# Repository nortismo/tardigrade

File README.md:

# Tardigrade

Tardigrade is an open hardware low-power board featuring NXP's LPC55S16 MCU, Semtech's SX1262 LoRa transceiver, u-blox's MAX-8Q GNSS module and Microchip's ATECC608A secure-element. It can be used as it is already or modified to your own needs. 

## Hardware

Schema and layout was created using [KiCad](https://kicad.org/).

## Software

There's a port of the official LoRaWAN stack implementation "LoRaMac-node" from Semtech for the Tardigrade board. The software is managed in a separate [GitHub repository](https://github.com/nortismo/LoRaMac-node).

## License

This hardware is licensed under the [TAPR Open Hardware License](https://tapr.org/the-tapr-open-hardware-license/). Please see the [LICENSE.txt](LICENSE.txt) file.

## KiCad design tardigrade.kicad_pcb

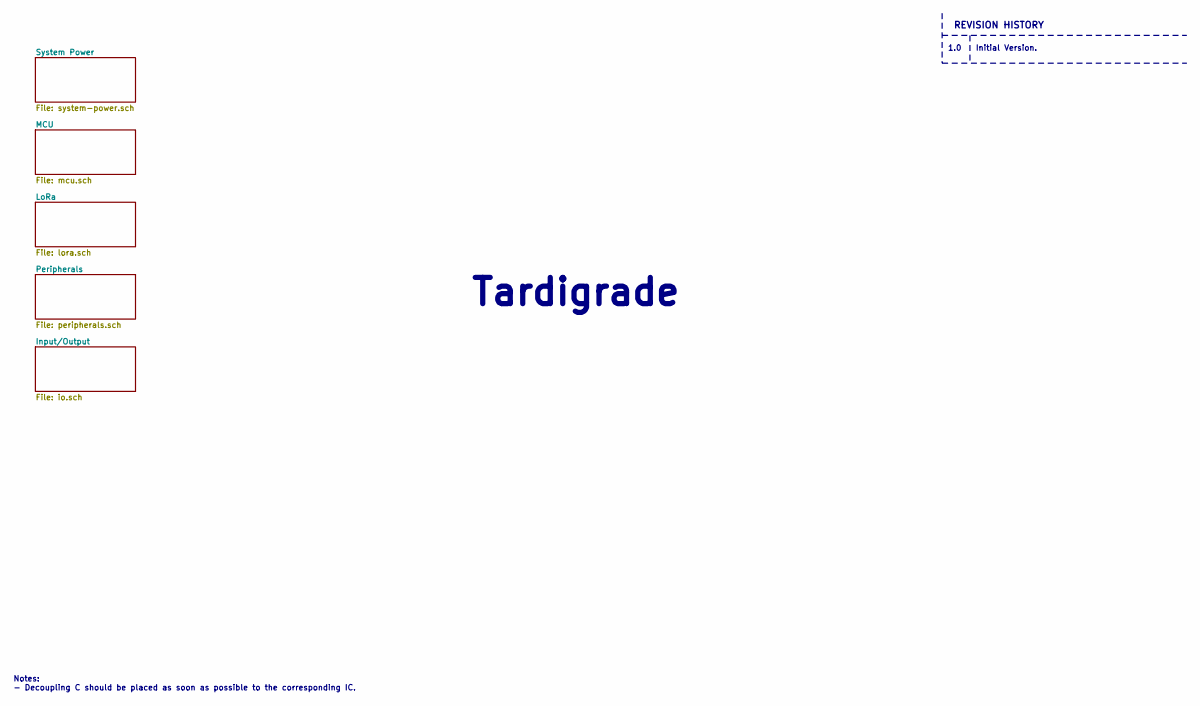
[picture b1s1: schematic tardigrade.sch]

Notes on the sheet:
REVISION HISTORY
1.0
Initial Version.
Tardigrade
Notes: - Decoupling C should be placed as soon as possible to the corresponding IC.

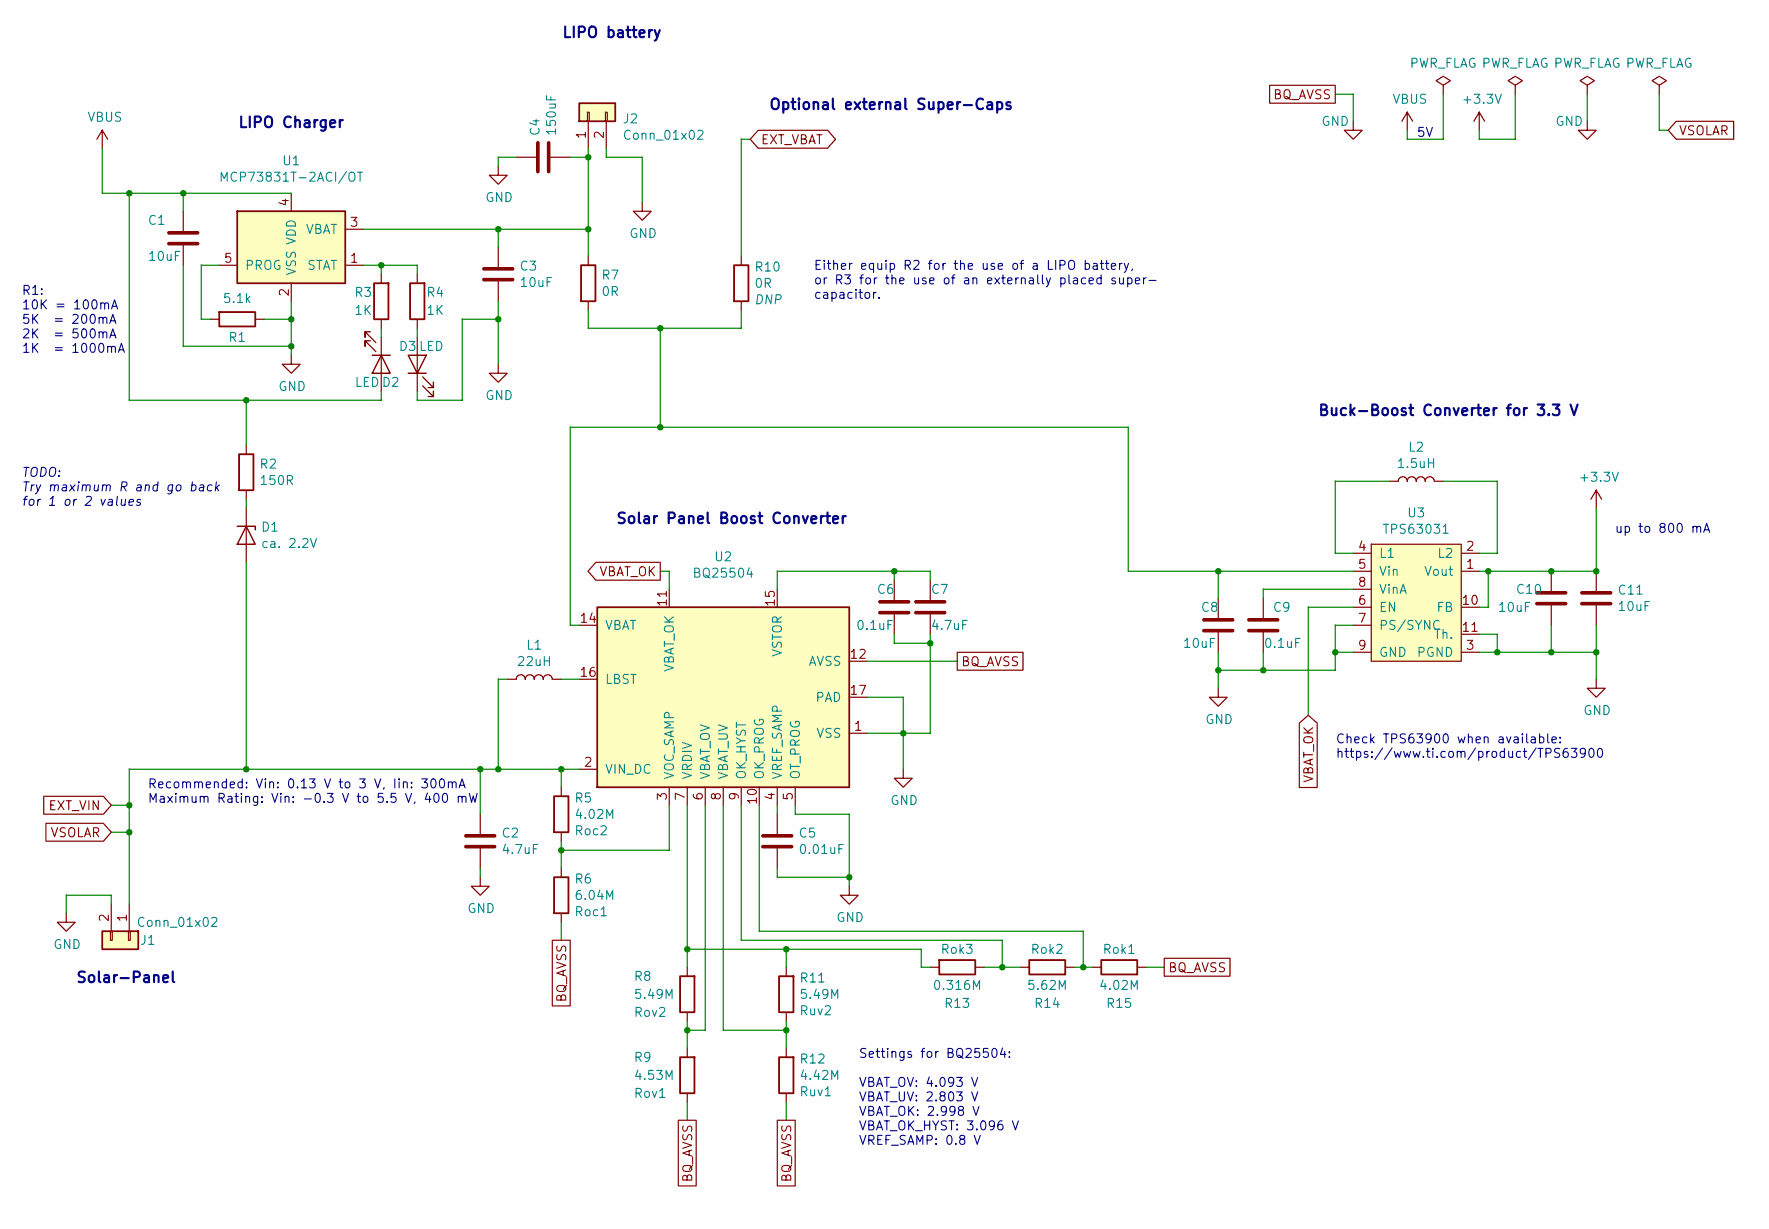
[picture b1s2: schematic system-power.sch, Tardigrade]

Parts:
C1, C3, C8, C10, C11: 10uF; C_0402_1005Metric
C2, C7: 4.7uF; C_0402_1005Metric
C4: 150uF; C_1206_3216Metric
C5: 0.01uF; C_0402_1005Metric
C6, C9: 0.1uF; C_0402_1005Metric
D1: ca. 2.2V; D_SOD-323
D2, D3: LED; LED_0603_1608Metric
J1, J2: Conn_01x02; JST_PH_S2B-PH-K_1x02_P2.00mm_Horizontal
L1: 22uH; L_0805_2012Metric
L2: 1.5uH; L_0402_1005Metric
R1: 5.1k; R_0402_1005Metric
R2: 150R; R_0402_1005Metric
R3, R4: 1K; R_0402_1005Metric
R5, R15: 4.02M; R_0402_1005Metric
R6: 6.04M; R_0402_1005Metric
R7, R10: 0R; R_0402_1005Metric
R8, R11: 5.49M; R_0402_1005Metric
R9: 4.53M; R_0402_1005Metric
R12: 4.42M; R_0402_1005Metric
R13: 0.316M; R_0402_1005Metric
R14: 5.62M; R_0402_1005Metric
U1: MCP73831T-2ACI/OT; SOT-23-5
U2: BQ25504; QFN50P300X300X100-17N-D
U3: TPS63031; TPS63031DSKR

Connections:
BQ_AVSS: C1.2, C2.2, C3.2, C4.1, C5.2, C6.2, C7.2, C8.2, C9.2, C10.2, C11.2, D3.1 (K), J1.2, J2.2, R1.1, R6.2, R9.1, R12.1, R15.2, U1.2 (VSS), U2.1 (VSS), U2.5 (OT_PROG), U2.12 (AVSS), U2.13 (VSS), U2.17 (PAD), U3.3 (PGND), U3.7 (PS/SYNC), U3.9 (GND), U3.11 (Th.); also elsewhere on the board
EXT_VBAT: R10.1; also elsewhere on the board
EXT_VIN: C2.1, D1.2 (A), J1.1, L1.1, R5.1, U2.2 (VIN_DC); also elsewhere on the board
unnamed: C3.1, C4.2, J2.1, R7.1, U1.3 (VBAT)
unnamed: C5.1, U2.4 (VREF_SAMP)
unnamed: C6.1, C7.1, U2.15 (VSTOR)
unnamed: C8.1, R7.2, R10.2, U2.14 (VBAT), U3.5 (Vin)
unnamed: C9.1, U3.8 (VinA)
unnamed: D1.1 (K), R2.2
unnamed: D2.1 (K), R3.1
unnamed: D3.2 (A), R4.1
unnamed: L1.2, U2.16 (LBST)
unnamed: L2.1, U3.4 (L1)
unnamed: L2.2, U3.2 (L2)
unnamed: R1.2, U1.5 (PROG)
unnamed: R3.2, R4.2, U1.1 (STAT)
unnamed: R5.2, R6.1, U2.3 (VOC_SAMP)
unnamed: R8.1, R9.2, U2.6 (VBAT_OV)
unnamed: R11.1, R12.2, U2.8 (VBAT_UV)
unnamed: R8.2, R11.2, R13.2, U2.7 (VRDIV)
unnamed: R13.1, R14.1, U2.9 (OK_HYST)
unnamed: R14.2, R15.1, U2.10 (OK_PROG)
VBAT_OK: U2.11 (VBAT_OK), U3.6 (EN); also elsewhere on the board
VBUS: C1.1, D2.2 (A), R2.1, U1.4 (VDD); also elsewhere on the board

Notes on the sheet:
R1: 10K = 100mA 5K = 200mA 2K = 500mA 1K = 1000mA
LIPO battery
Optional external Super-Caps
up to 800 mA
Recommended: Vin: 0.13 V to 3 V, Iin: 300mA Maximum Rating: Vin: -0.3 V to 5.5 V, 400 mW
Check TPS63900 when available: https://www.ti.com/product/TPS63900
LIPO Charger
Solar-Panel
Solar Panel Boost Converter
Buck-Boost Converter for 3.3 V
Settings for BQ25504: VBAT_OV: 4.093 V VBAT_UV: 2.803 V VBAT_OK: 2.998 V VBAT_OK_HYST: 3.096 V VREF_SAMP: 0.8 V
Either equip R2 for the use of a LIPO battery, or R3 for the use of an externally placed super- capacitor.
TODO: Try maximum R and go back for 1 or 2 values

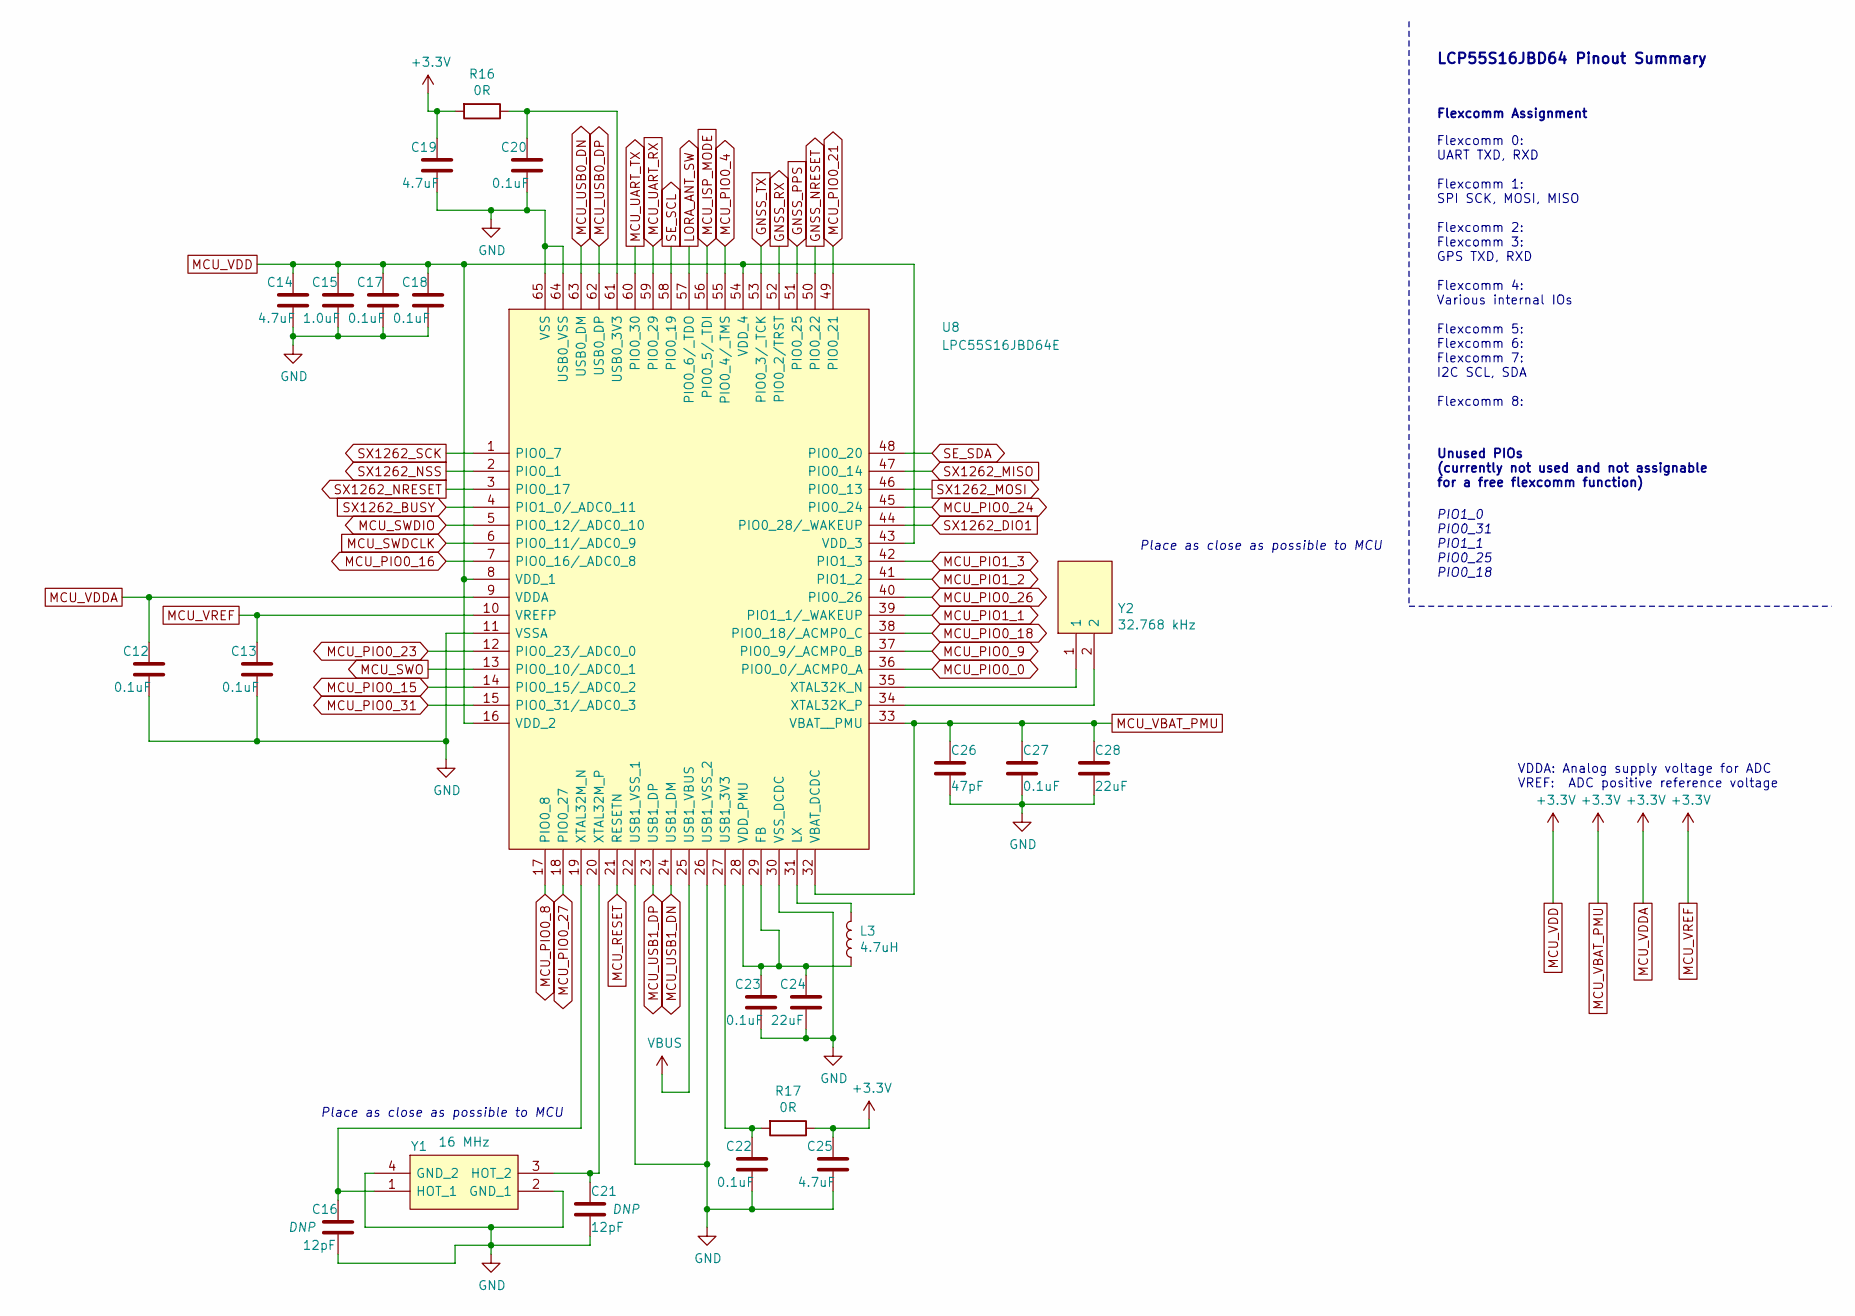
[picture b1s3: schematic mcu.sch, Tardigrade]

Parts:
C12, C13, C17, C18, C20, C22, C23, C27: 0.1uF; C_0402_1005Metric
C14, C19, C25: 4.7uF; C_0402_1005Metric
C15: 1.0uF; C_0402_1005Metric
C16, C21: 12pF; C_0402_1005Metric
C24, C28: 22uF; C_0603_1608Metric
C26: 47pF; C_0402_1005Metric
L3: 4.7uH; L_0805_2012Metric
R16, R17: 0R; R_0402_1005Metric
U8: LPC55S16JBD64E; QFP50P1200X1200X120-65N; Manufacturer_Part_Number LPC55S16JBD64E; Mouser Part Number 771-LPC55S16JBD64E
Y1: 16 MHz; CX3225SA16000
Y2: 32.768 kHz; FC-135_1; Manufacturer_Part_Number FC-135 32.7680KA-AG3; Mouser Part Number 732-FC135-32.76KAAG3

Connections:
BQ_AVSS: C12.2, C13.2, C14.2, C15.2, C16.2, C17.2, C18.2, C19.2, C20.2, C21.2, C22.2, C23.2, C24.2, C25.2, C26.2, C27.2, C28.2, U8.11 (VSSA), U8.22 (USB1_VSS_1), U8.26 (USB1_VSS_2), U8.30 (VSS_DCDC), U8.64 (USB0_VSS), U8.65 (VSS), Y1.2 (GND_1), Y1.4 (GND_2); also elsewhere on the board
GNSS_NRESET: U8.50 (PIO0_22); also elsewhere on the board
GNSS_PPS: U8.51 (PIO0_25); also elsewhere on the board
GNSS_RX: U8.52 (PIO0_2/TRST); also elsewhere on the board
GNSS_TX: U8.53 (PIO0_3/_TCK); also elsewhere on the board
LORA_ANT_SW: U8.57 (PIO0_6/_TDO); also elsewhere on the board
MCU_ISP_MODE: U8.56 (PIO0_5/_TDI); also elsewhere on the board
MCU_PIO0_0: U8.36 (PIO0_0/_ACMP0_A); also elsewhere on the board
MCU_PIO0_4: U8.55 (PIO0_4/_TMS); also elsewhere on the board
MCU_PIO0_8: U8.17 (PIO0_8); also elsewhere on the board
MCU_PIO0_9: U8.37 (PIO0_9/_ACMP0_B); also elsewhere on the board
MCU_PIO0_15: U8.14 (PIO0_15/_ADC0_2); also elsewhere on the board
MCU_PIO0_16: U8.7 (PIO0_16/_ADC0_8); also elsewhere on the board
MCU_PIO0_18: U8.38 (PIO0_18/_ACMP0_C); also elsewhere on the board
MCU_PIO0_21: U8.49 (PIO0_21); also elsewhere on the board
MCU_PIO0_23: U8.12 (PIO0_23/_ADC0_0); also elsewhere on the board
MCU_PIO0_24: U8.45 (PIO0_24); also elsewhere on the board
MCU_PIO0_26: U8.40 (PIO0_26); also elsewhere on the board
MCU_PIO0_27: U8.18 (PIO0_27); also elsewhere on the board
MCU_PIO0_31: U8.15 (PIO0_31/_ADC0_3); also elsewhere on the board
MCU_PIO1_1: U8.39 (PIO1_1/_WAKEUP); also elsewhere on the board
MCU_PIO1_2: U8.41 (PIO1_2); also elsewhere on the board
MCU_PIO1_3: U8.42 (PIO1_3); also elsewhere on the board
MCU_RESET: U8.21 (RESETN); also elsewhere on the board
MCU_SWDCLK: U8.6 (PIO0_11/_ADC0_9); also elsewhere on the board
MCU_SWDIO: U8.5 (PIO0_12/_ADC0_10); also elsewhere on the board
MCU_SWO: U8.13 (PIO0_10/_ADC0_1); also elsewhere on the board
MCU_UART_RX: U8.59 (PIO0_29); also elsewhere on the board
MCU_UART_TX: U8.60 (PIO0_30); also elsewhere on the board
MCU_USB0_DN: U8.63 (USB0_DM); also elsewhere on the board
MCU_USB0_DP: U8.62 (USB0_DP); also elsewhere on the board
MCU_USB1_DN: U8.24 (USB1_DM); also elsewhere on the board
MCU_USB1_DP: U8.23 (USB1_DP); also elsewhere on the board
unnamed: C16.1, U8.19 (XTAL32M_N), Y1.1 (HOT_1)
unnamed: C20.1, R16.1, U8.61 (USB0_3V3)
unnamed: C21.1, U8.20 (XTAL32M_P), Y1.3 (HOT_2)
unnamed: C22.1, R17.2, U8.27 (USB1_3V3)
unnamed: C23.1, C24.1, L3.1, U8.28 (VDD_PMU), U8.29 (FB)
unnamed: L3.2, U8.31 (LX)
unnamed: U8.34 (XTAL32K_P), Y2.2
unnamed: U8.35 (XTAL32K_N), Y2.1
SE_SCL: U8.58 (PIO0_19); also elsewhere on the board
SE_SDA: U8.48 (PIO0_20); also elsewhere on the board
SX1262_BUSY: U8.4 (PIO1_0/_ADC0_11); also elsewhere on the board
SX1262_DIO1: U8.44 (PIO0_28/_WAKEUP); also elsewhere on the board
SX1262_MISO: U8.47 (PIO0_14); also elsewhere on the board
SX1262_MOSI: U8.46 (PIO0_13); also elsewhere on the board
SX1262_NRESET: U8.3 (PIO0_17); also elsewhere on the board
SX1262_NSS: U8.2 (PIO0_1); also elsewhere on the board
SX1262_SCK: U8.1 (PIO0_7); also elsewhere on the board
VBUS: U8.25 (USB1_VBUS); also elsewhere on the board

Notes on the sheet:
Flexcomm 0: UART TXD, RXD Flexcomm 1: SPI SCK, MOSI, MISO Flexcomm 2: Flexcomm 3: GPS TXD, RXD Flexcomm 4: Various internal IOs Flexcomm 5: Flexcomm 6: Flexcomm 7: I2C SCL, SDA Flexcomm 8:
PIO1_0 PIO0_31 PIO1_1 PIO0_25 PIO0_18
LCP55S16JBD64 Pinout Summary
Flexcomm Assignment
Unused PIOs (currently not used and not assignable for a free flexcomm function)
Place as close as possible to MCU
VDDA: Analog supply voltage for ADC VREF: ADC positive reference voltage

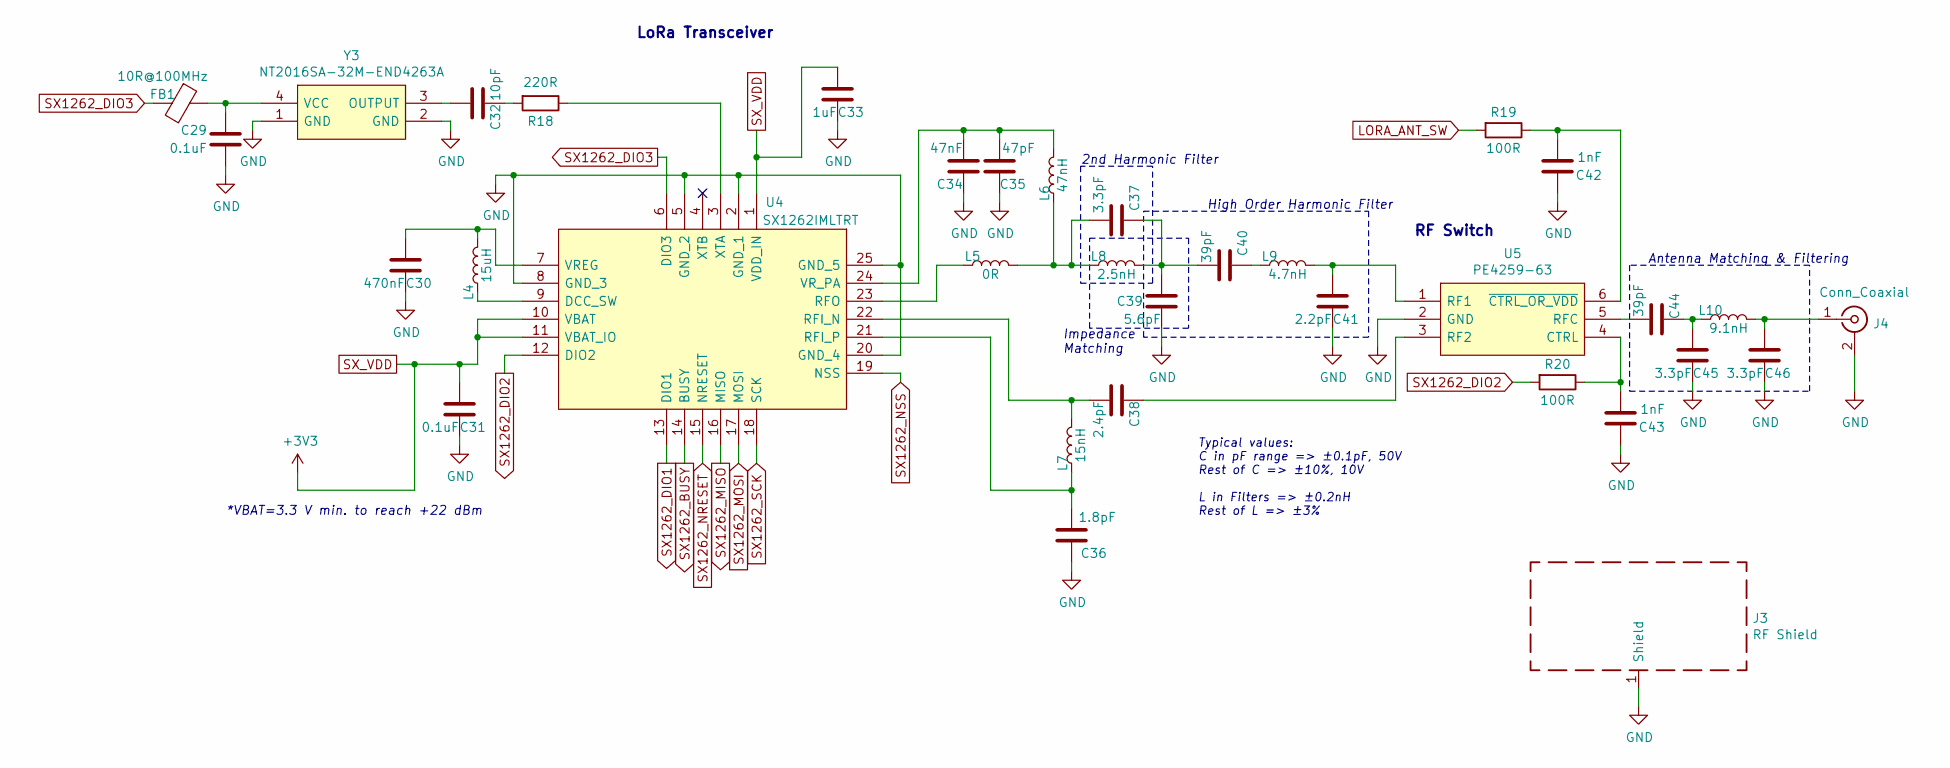
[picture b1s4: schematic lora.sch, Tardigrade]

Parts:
C29, C31: 0.1uF; C_0402_1005Metric
C30: 470nF; C_0402_1005Metric
C32: 10pF; C_0402_1005Metric
C33: 1uF; C_0402_1005Metric
C34: 47nF; C_0402_1005Metric
C35: 47pF; C_0402_1005Metric
C36: 1.8pF; C_0402_1005Metric
C37, C45, C46: 3.3pF; C_0402_1005Metric
C38: 2.4pF; C_0402_1005Metric
C39: 5.6pF; C_0402_1005Metric
C40, C44: 39pF; C_0402_1005Metric
C41: 2.2pF; C_0402_1005Metric
C42, C43: 1nF; C_0402_1005Metric
FB1: 10R@100MHz; C_0402_1005Metric
J3: RF Shield; Laird_Technologies_BMI-S-209-F_29.36x18.50mm
J4: Conn_Coaxial; U.FL_Hirose_U.FL-R-SMT-1_Vertical
L4: 15uH; L_0805_2012Metric
L5: 0R; L_0402_1005Metric
L6: 47nH; L_0402_1005Metric
L7: 15nH; L_0402_1005Metric
L8: 2.5nH; L_0402_1005Metric
L9: 4.7nH; L_0402_1005Metric
L10: 9.1nH; L_0402_1005Metric
R18: 220R; R_0402_1005Metric
R19, R20: 100R; R_0402_1005Metric
U4: SX1262IMLTRT; QFN50P400X400X100-25N-D; Manufacturer_Part_Number SX1262IMLTRT; Mouser Part Number 947-SX1262IMLTRT
U5: PE4259-63; SOT65P210X110-6N; Manufacturer_Part_Number PE4259-63
Y3: NT2016SA-32M-END4263A; NT2016SA; Manufacturer_Part_Number NT2016SA-32M-END4263A

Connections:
BQ_AVSS: C29.1, C30.1, C31.1, C33.1, C34.1, C35.1, C36.1, C39.1, C41.1, C42.1, C43.1, C45.1, C46.1, J3.1, J4.2 (Ext), U4.2 (GND_1), U4.5 (GND_2), U4.8 (GND_3), U4.20 (GND_4), U4.25 (GND_5), U5.2 (GND), Y3.1 (GND), Y3.2 (GND); also elsewhere on the board
LORA_ANT_SW: R19.2; also elsewhere on the board
unnamed: C29.2, FB1.1, Y3.4 (VCC)
unnamed: C30.2, L4.2, U4.7 (VREG)
unnamed: C32.1, R18.2
unnamed: C32.2, Y3.3 (OUTPUT)
unnamed: C34.2, C35.2, L6.2, U4.24 (VR_PA)
unnamed: C36.2, L7.1, U4.21 (RFI_P)
unnamed: C37.1, C39.2, C40.2, L8.2
unnamed: C37.2, L5.2, L6.1, L8.1
unnamed: C38.1, U5.3 (RF2)
unnamed: C38.2, L7.2, U4.22 (RFI_N)
unnamed: C40.1, L9.1
unnamed: C41.2, L9.2, U5.1 (RF1)
unnamed: C42.2, R19.1, U5.6 (~CTRL_OR_VDD)
unnamed: C43.2, R20.1, U5.4 (CTRL)
unnamed: C44.1, C45.2, L10.1
unnamed: C44.2, U5.5 (RFC)
unnamed: C46.2, J4.1 (In), L10.2
unnamed: L4.1, U4.9 (DCC_SW)
unnamed: L5.1, U4.23 (RFO)
unnamed: R18.1, U4.3 (XTA)
SX1262_BUSY: U4.14 (BUSY); also elsewhere on the board
SX1262_DIO1: U4.13 (DIO1); also elsewhere on the board
SX1262_DIO2: R20.2, U4.12 (DIO2)
SX1262_DIO3: FB1.2, U4.6 (DIO3)
SX1262_MISO: U4.16 (MISO); also elsewhere on the board
SX1262_MOSI: U4.17 (MOSI); also elsewhere on the board
SX1262_NRESET: U4.15 (NRESET); also elsewhere on the board
SX1262_NSS: U4.19 (NSS); also elsewhere on the board
SX1262_SCK: U4.18 (SCK); also elsewhere on the board

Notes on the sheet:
RF Switch
*VBAT=3.3 V min. to reach +22 dBm
LoRa Transceiver
2nd Harmonic Filter
Impedance Matching
High Order Harmonic Filter
Antenna Matching & Filtering
Typical values: C in pF range => ±0.1pF, 50V Rest of C => ±10%, 10V L in Filters => ±0.2nH Rest of L => ±3%

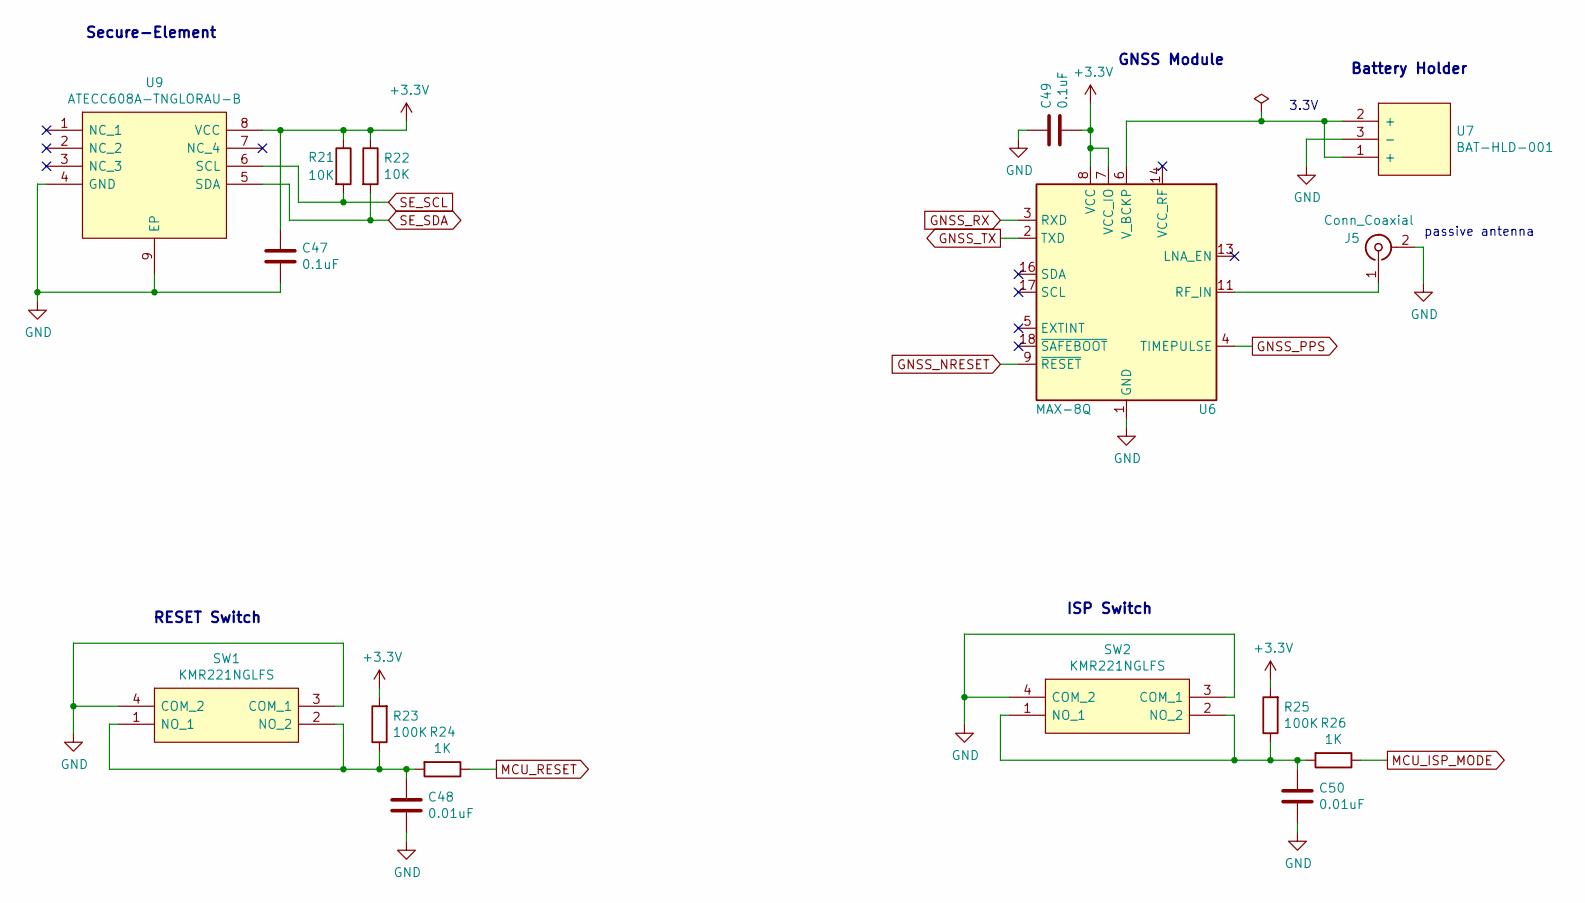
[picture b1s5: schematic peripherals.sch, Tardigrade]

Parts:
C47, C49: 0.1uF; C_0402_1005Metric
C48, C50: 0.01uF; C_0402_1005Metric
J5: Conn_Coaxial; U.FL_Hirose_U.FL-R-SMT-1_Vertical
R21, R22: 10K; R_0402_1005Metric
R23, R25: 100K; R_0402_1005Metric
R24, R26: 1K; R_0402_1005Metric
SW1, SW2: KMR221NGLFS; Manufacturer_Part_Number KMR221NGLFS; Mouser Part Number 611-KMR221NGLFS
U6: MAX-8Q; ublox_MAX
U7: BAT-HLD-001; BATHLD001; Manufacturer_Part_Number BAT-HLD-001; Mouser Part Number 712-BAT-HLD-001
U9: ATECC608A-TNGLORAU-B; SON50P300X200X60-9N; Manufacturer_Part_Number ATECC608A-TNGLORAU-B

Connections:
BQ_AVSS: C47.2, C48.2, C49.1, C50.2, J5.2 (Ext), SW1.3 (COM_1), SW1.4 (COM_2), SW2.3 (COM_1), SW2.4 (COM_2), U6.1 (GND), U6.10 (GND), U6.12 (GND), U7.3 (-), U9.4 (GND), U9.9 (EP); also elsewhere on the board
GNSS_NRESET: U6.9 (~RESET); also elsewhere on the board
GNSS_PPS: U6.4 (TIMEPULSE); also elsewhere on the board
GNSS_RX: U6.3 (RXD); also elsewhere on the board
GNSS_TX: U6.2 (TXD); also elsewhere on the board
MCU_ISP_MODE: R26.1; also elsewhere on the board
MCU_RESET: R24.1; also elsewhere on the board
unnamed: C48.1, R23.1, R24.2, SW1.1 (NO_1), SW1.2 (NO_2)
unnamed: C50.1, R25.1, R26.2, SW2.1 (NO_1), SW2.2 (NO_2)
unnamed: J5.1 (In), U6.11 (RF_IN)
unnamed: U6.6 (V_BCKP), U7.1 (+), U7.2 (+)
SE_SCL: R21.2, U9.6 (SCL); also elsewhere on the board
SE_SDA: R22.2, U9.5 (SDA); also elsewhere on the board

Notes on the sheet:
Secure-Element
GNSS Module
RESET Switch
ISP Switch
Battery Holder
3.3V
passive antenna

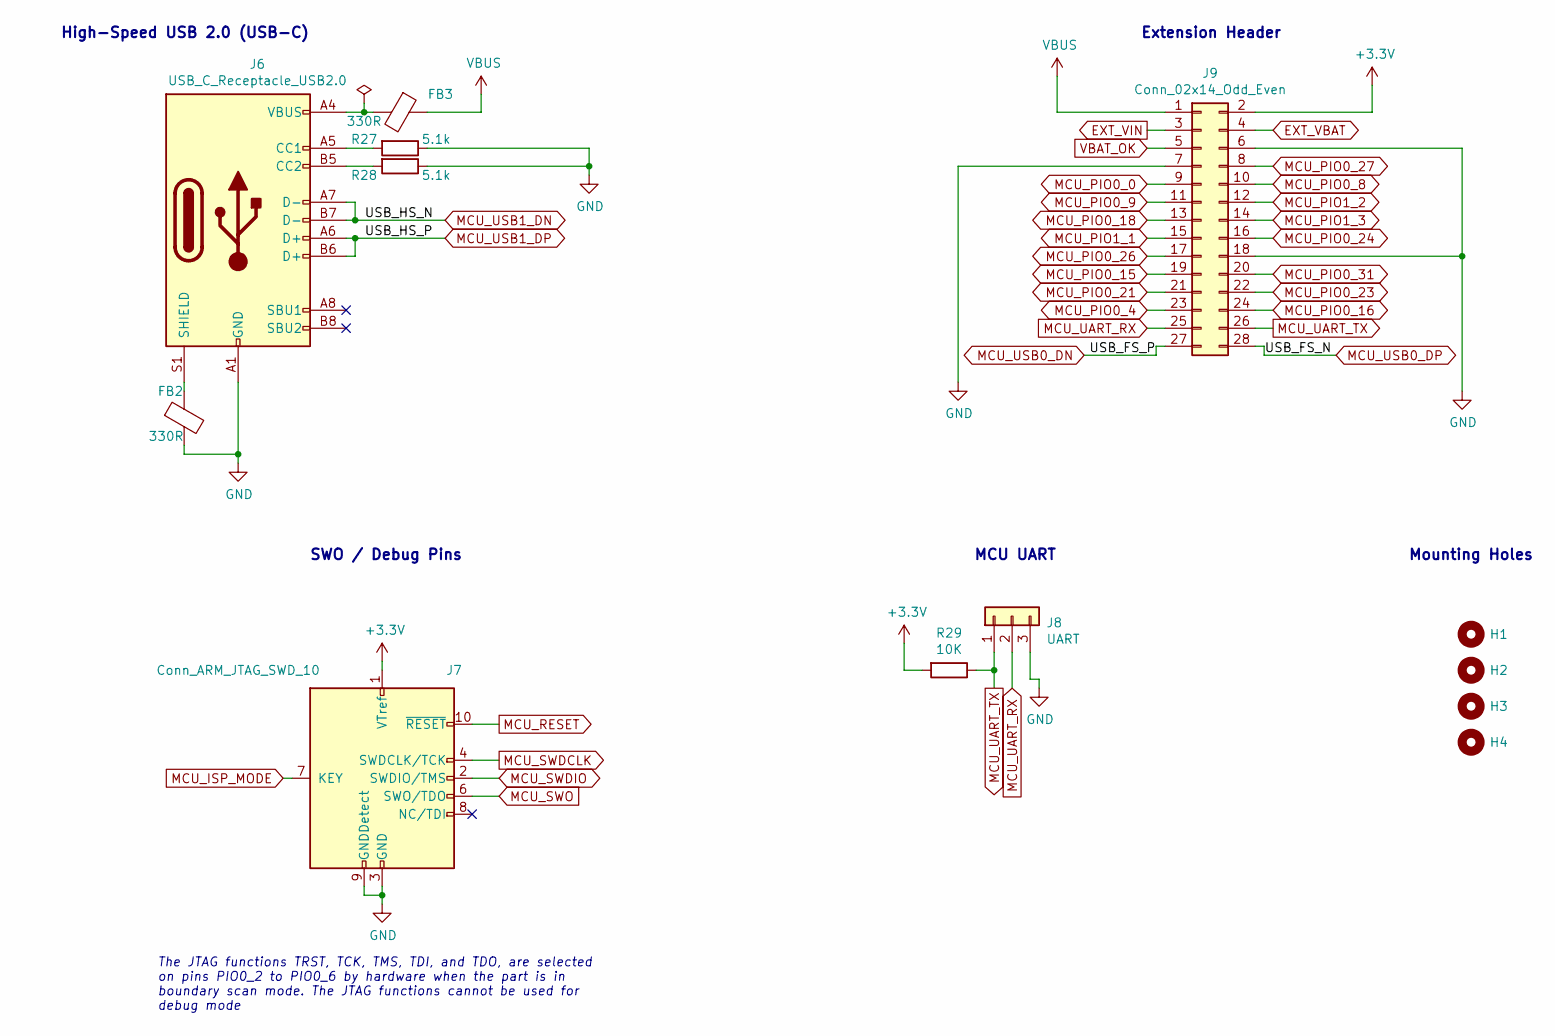
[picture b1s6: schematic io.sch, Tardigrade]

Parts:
FB2, FB3: 330R; C_0402_1005Metric
H1, H2, H3, H4: MountingHole; MountingHole_2.2mm_M2_Pad
J6: USB_C_Receptacle_USB2.0; USB_C_Receptacle_JAE_DX07S016JA1
J7: Conn_ARM_JTAG_SWD_10; PinHeader_2x05_P1.27mm_Vertical
J8: UART; PinHeader_1x03_P2.54mm_Vertical
J9: Conn_02x14_Odd_Even; PinHeader_2x14_P2.54mm_Vertical
R27, R28: 5.1k; R_0402_1005Metric
R29: 10K; R_0402_1005Metric

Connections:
BQ_AVSS: FB2.2, J6.A1 (GND), J6.A12 (GND), J6.B1 (GND), J6.B12 (GND), J7.3 (GND), J7.5 (GND), J7.9 (GNDDetect), J8.3, J9.6, J9.7, J9.18, R27.1, R28.1; also elsewhere on the board
EXT_VBAT: J9.4; also elsewhere on the board
EXT_VIN: J9.3; also elsewhere on the board
MCU_ISP_MODE: J7.7 (KEY); also elsewhere on the board
MCU_PIO0_0: J9.9; also elsewhere on the board
MCU_PIO0_4: J9.23; also elsewhere on the board
MCU_PIO0_8: J9.10; also elsewhere on the board
MCU_PIO0_9: J9.11; also elsewhere on the board
MCU_PIO0_15: J9.19; also elsewhere on the board
MCU_PIO0_16: J9.24; also elsewhere on the board
MCU_PIO0_18: J9.13; also elsewhere on the board
MCU_PIO0_21: J9.21; also elsewhere on the board
MCU_PIO0_23: J9.22; also elsewhere on the board
MCU_PIO0_24: J9.16; also elsewhere on the board
MCU_PIO0_26: J9.17; also elsewhere on the board
MCU_PIO0_27: J9.8; also elsewhere on the board
MCU_PIO0_31: J9.20; also elsewhere on the board
MCU_PIO1_1: J9.15; also elsewhere on the board
MCU_PIO1_2: J9.12; also elsewhere on the board
MCU_PIO1_3: J9.14; also elsewhere on the board
MCU_RESET: J7.10 (~RESET~); also elsewhere on the board
MCU_SWDCLK: J7.4 (SWDCLK/TCK); also elsewhere on the board
MCU_SWDIO: J7.2 (SWDIO/TMS); also elsewhere on the board
MCU_SWO: J7.6 (SWO/TDO); also elsewhere on the board
MCU_UART_RX: J8.2, J9.25; also elsewhere on the board
MCU_UART_TX: J8.1, J9.26, R29.1; also elsewhere on the board
MCU_USB0_DN: J9.27; also elsewhere on the board
MCU_USB0_DP: J9.28; also elsewhere on the board
MCU_USB1_DN: J6.A7 (D-), J6.B7 (D-); also elsewhere on the board
MCU_USB1_DP: J6.A6 (D+), J6.B6 (D+); also elsewhere on the board
unnamed: FB2.1, J6.S1 (SHIELD)
unnamed: FB3.2, J6.A4 (VBUS), J6.A9 (VBUS), J6.B4 (VBUS), J6.B9 (VBUS)
unnamed: J6.A5 (CC1), R27.2
unnamed: J6.B5 (CC2), R28.2
VBAT_OK: J9.5; also elsewhere on the board
VBUS: FB3.1, J9.1; also elsewhere on the board

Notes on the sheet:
The JTAG functions TRST, TCK, TMS, TDI, and TDO, are selected on pins PIO0_2 to PIO0_6 by hardware when the part is in boundary scan mode. The JTAG functions cannot be used for debug mode
SWO / Debug Pins
High-Speed USB 2.0 (USB-C)
MCU UART
Extension Header
Mounting Holes

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
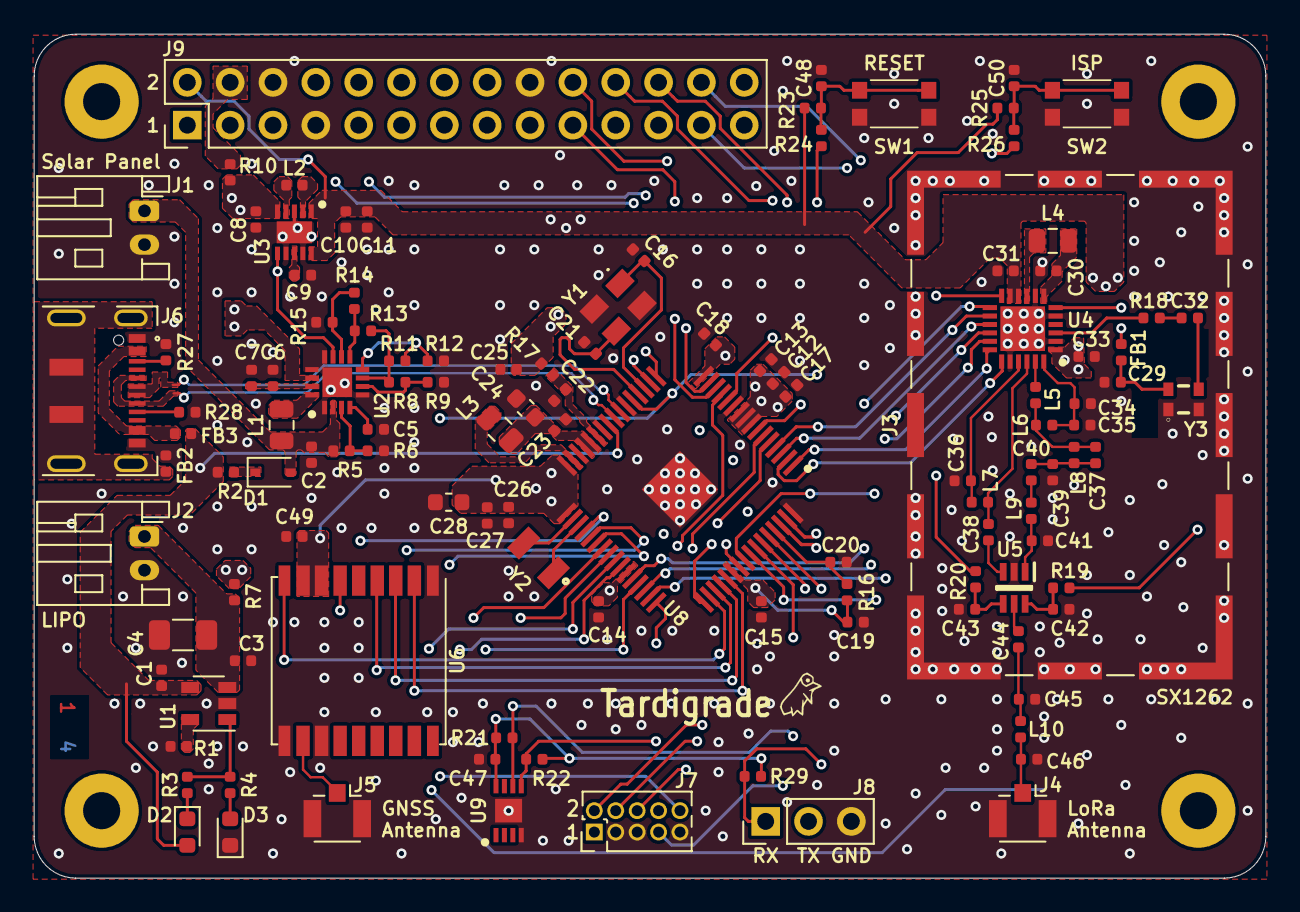
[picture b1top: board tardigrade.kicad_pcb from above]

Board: 4 copper layers, 73.0 x 50.0 mm, 122 parts (1 on the bottom side), 104 nets.

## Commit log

2020-10-05 Fixed wrong link in readme
2020-10-30 Added notes for new design
2020-11-05 Fixed issue #2, #3, #4 and #5
2020-11-05 Issue #6 - Fixed wrong placement of C21
2020-11-05 Removed unnecessary leds from system-power to save power
2020-11-05 Removed jumpers from system-power
2020-11-05 Removed BAT_OK signal from MCU
2020-11-05 Removed jumpers from mcu
2020-11-05 Removed jumpers from peripherals
2020-11-05 Removed jumpers from ios
2020-11-05 Changed extension header symbol
2020-11-05 Changed all symbols names from IC to U
2020-11-05 Unnecessary note removed
2020-11-05 Changed pin assignment on mcu and extension header
2020-11-05 Changed order of input capacitance to bq
2020-11-05 Added footprint assignment
2020-11-06 Review done
2020-11-12 Major change of the layout (reviewed) for V1.1
2020-11-12 Updated headers/footers of files
2020-12-17 Changed notes on system power schematic
2020-12-18 Added revision comment on schema
2021-11-08 Update README.md
    https://forum.kicad.info/t/warning-avoid-all-links-to-kicad-pcb-org-use-kicad-org/31521
